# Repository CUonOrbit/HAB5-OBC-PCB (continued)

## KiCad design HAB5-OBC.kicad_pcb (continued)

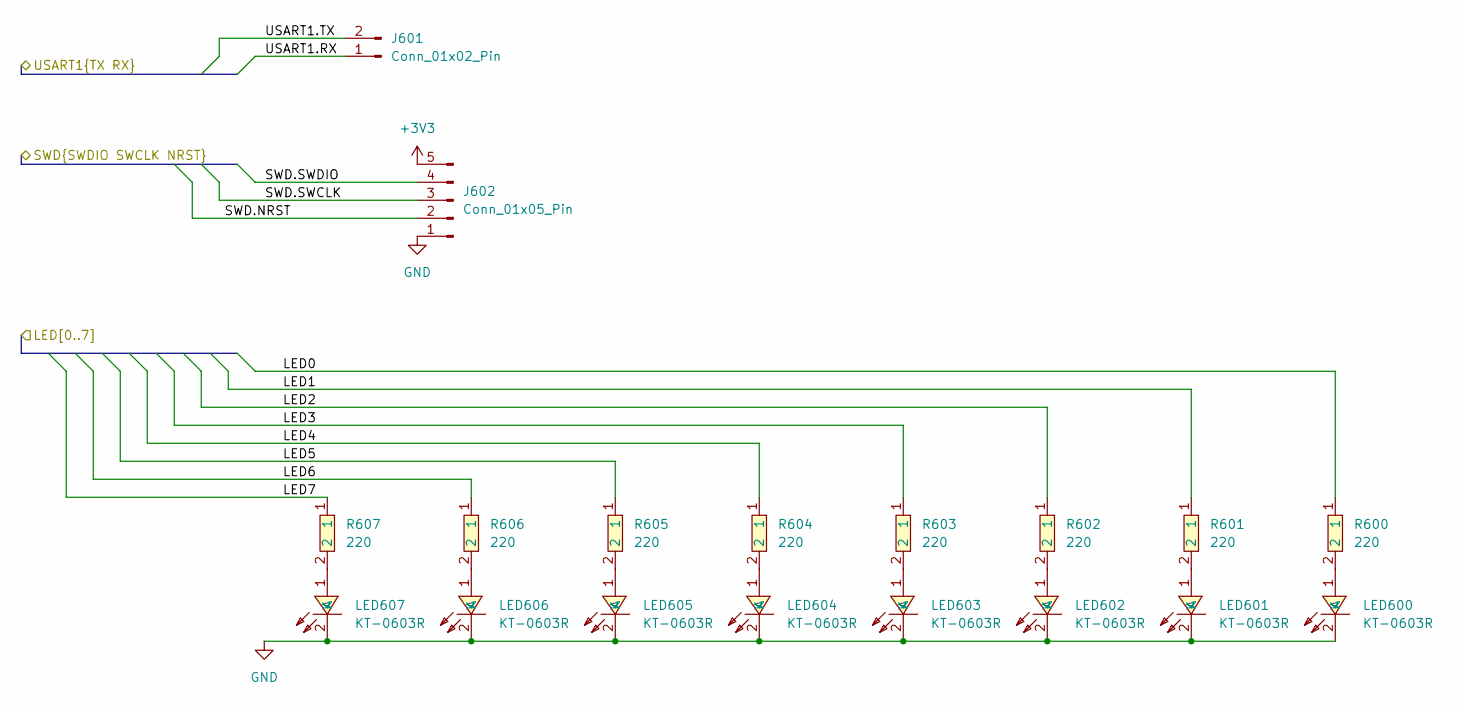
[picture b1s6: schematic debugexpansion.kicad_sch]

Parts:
J601: Conn_01x02_Pin; PinHeader_1x02_P2.54mm_Vertical
J602: Conn_01x05_Pin; PinHeader_1x05_P2.54mm_Vertical
LED600, LED601, LED602, LED603, LED604, LED605, LED606, LED607: KT-0603R; LED-SMD_L1.6-W0.8-R-RD; MPN KT-0603R; LCSC Part C2286
R600, R601, R602, R603, R604, R605, R606, R607: 220; R0603; MPN 0603WAF2200T5E; LCSC Part C22962

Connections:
+3V3: J602.5; also elsewhere on the board
/Debug and Expansion/LED0: R600.1; also elsewhere on the board
/Debug and Expansion/LED1: R601.1; also elsewhere on the board
/Debug and Expansion/LED2: R602.1; also elsewhere on the board
/Debug and Expansion/LED3: R603.1; also elsewhere on the board
/Debug and Expansion/LED4: R604.1; also elsewhere on the board
/Debug and Expansion/LED5: R605.1; also elsewhere on the board
/Debug and Expansion/LED6: R606.1; also elsewhere on the board
/Debug and Expansion/LED7: R607.1; also elsewhere on the board
/Debug and Expansion/SWD.NRST: J602.2; also elsewhere on the board
/Debug and Expansion/SWD.SWCLK: J602.3; also elsewhere on the board
/Debug and Expansion/SWD.SWDIO: J602.4; also elsewhere on the board
/Debug and Expansion/USART1.RX: J601.1; also elsewhere on the board
/Debug and Expansion/USART1.TX: J601.2; also elsewhere on the board
GND: J602.1, LED600.2 (K), LED601.2 (K), LED602.2 (K), LED603.2 (K), LED604.2 (K), LED605.2 (K), LED606.2 (K), LED607.2 (K); also elsewhere on the board
unnamed: LED600.1 (A), R600.2
unnamed: LED601.1 (A), R601.2
unnamed: LED602.1 (A), R602.2
unnamed: LED603.1 (A), R603.2
unnamed: LED604.1 (A), R604.2
unnamed: LED605.1 (A), R605.2
unnamed: LED606.1 (A), R606.2
unnamed: LED607.1 (A), R607.2

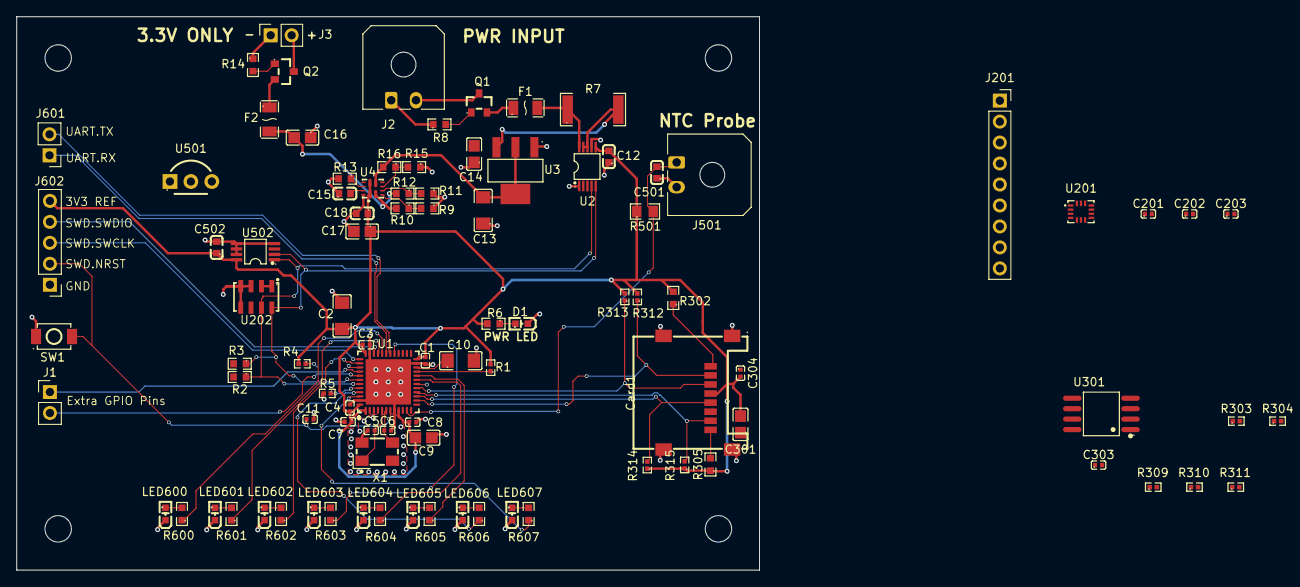
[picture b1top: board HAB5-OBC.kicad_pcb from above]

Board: 4 copper layers, 90.0 x 67.0 mm, 94 parts (0 on the bottom side), 65 nets.
